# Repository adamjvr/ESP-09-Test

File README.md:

# ESP-09-Test
A simple quick breakout board to test the functionality of the ESP-09 ESP8266 module. Designed to test the modules functionality in comparison to the ESP-12E module used in the SunLEaf prototypes and the version 1 PCB that was modified.

KiCAD 3D Renders

OSHPark Board Renders

Top

Bottom

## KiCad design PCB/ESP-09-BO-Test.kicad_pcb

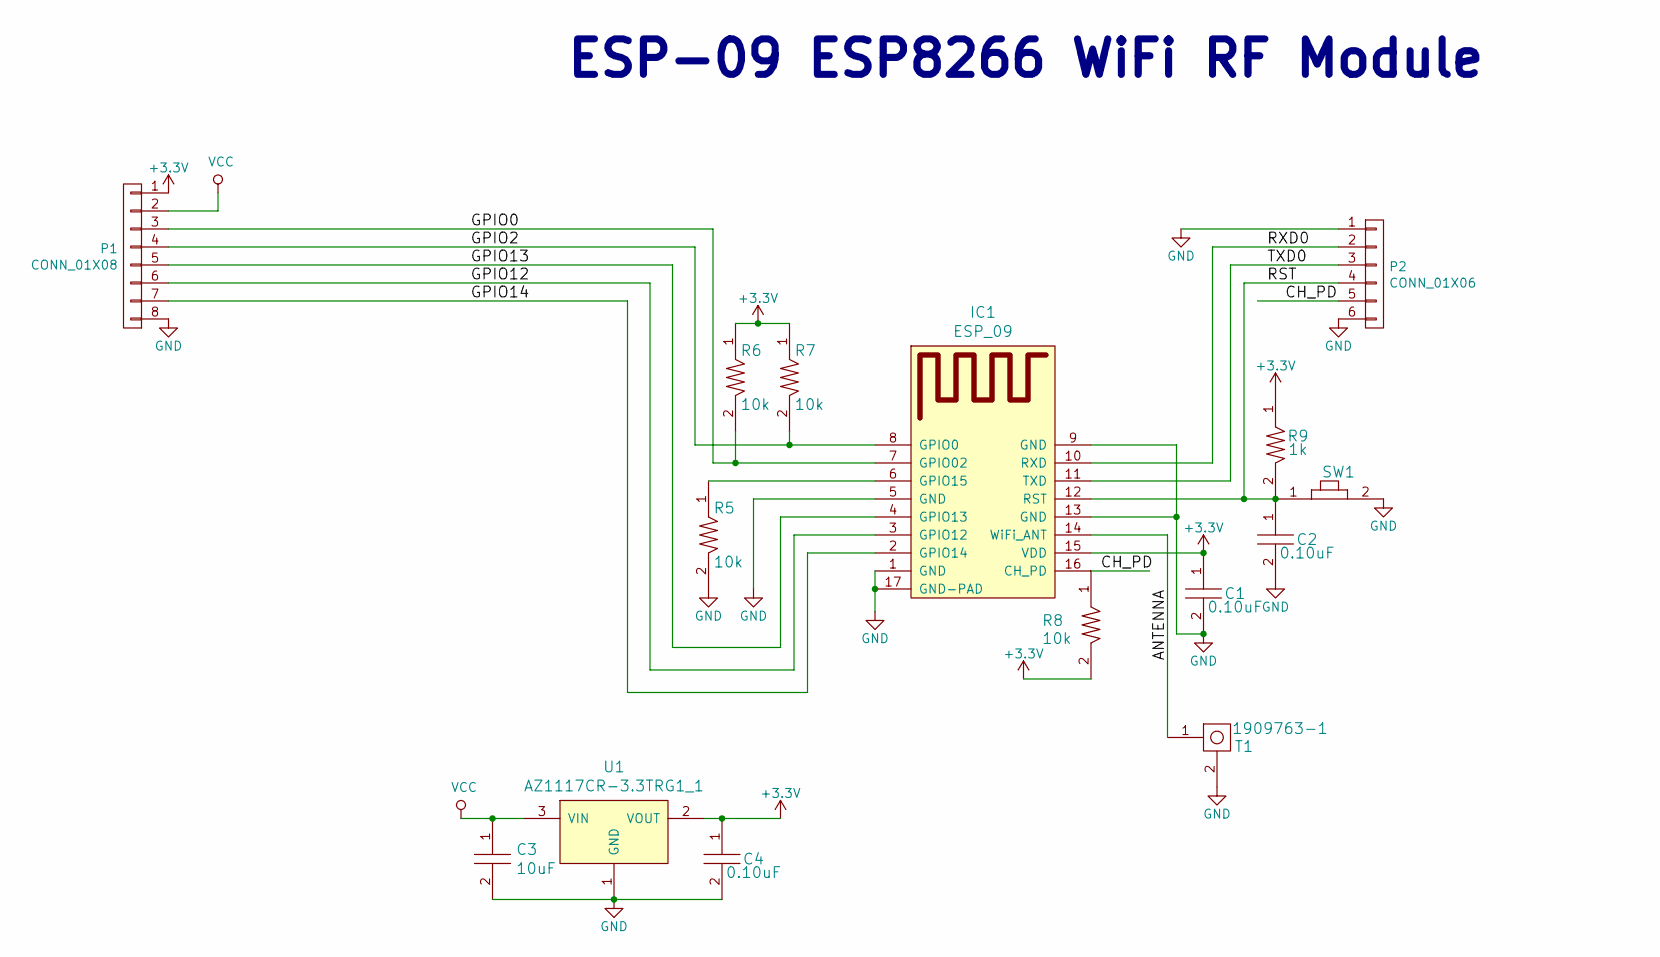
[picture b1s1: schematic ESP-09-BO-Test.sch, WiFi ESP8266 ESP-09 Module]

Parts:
C1, C2, C4: CL05B104JP5NNNC; C0402; Tolerance 5%; Voltage 10V; MFR# CL05B104JP5NNNC
C3: CL10A106KQ8NNNC; C0603; Tolerance 10%; Voltage 6.3V; MFR# CL10A106KQ8NNNC
IC1: ESP_09; ESP-09
P1: CONN_01X08; Pin_Header_Straight_1x08
P2: CONN_01X06; Pin_Header_Straight_1x06
R5, R6, R7, R8: RC1005F103CS; R0402; Tolerance 1%; Voltage N/A; MFR# RC1005F103CS
R9: RC1005F102CS; R0402; Tolerance %; Voltage N/A; MFR# RC1005F102CS
SW1: B3U-1000P; Tolerance %; Voltage 50V; MFR# B3U-1000P
T1: 1909763-1; Tolerance N/A; Voltage N/A; MFR# 1909763-1
U1: AZ1117CR-3.3TRG1_1; AZ1117CR-3.3TRG1; Tolerance N/A; Voltage 3.7V input 3.3V Output; MFR# AZ1117CR-3.3TRG1

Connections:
+3V3: C1.1, C4.1, IC1.15 (VDD), P1.1, R6.1, R7.1, R8.2, R9.1, U1.2 (VOUT)
/ANTENNA: IC1.14 (WiFi_ANT), T1.1
/CH_PD: IC1.16 (CH_PD), P2.5, R8.1
/GPIO0: IC1.7 (GPIO02), P1.3, R6.2
/GPIO2: IC1.8 (GPIO0), P1.4, R7.2
/GPIO12: IC1.3 (GPIO12), P1.6
/GPIO13: IC1.4 (GPIO13), P1.5
/GPIO14: IC1.2 (GPIO14), P1.7
/RST: C2.1, IC1.12 (RST), P2.4, R9.2, SW1.1
/RXD0: IC1.10 (RXD), P2.2
/TXD0: IC1.11 (TXD), P2.3
GND: C1.2, C2.2, C3.2, C4.2, IC1.1 (GND), IC1.5 (GND), IC1.9 (GND), IC1.13 (GND), IC1.17 (GND-PAD), P1.8, P2.1, P2.6, R5.2, SW1.2, T1.2, U1.1 (GND)
unnamed: IC1.6 (GPIO15), R5.1
VCC: C3.1, P1.2, U1.3 (VIN)

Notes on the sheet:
ESP-09 ESP8266 WiFi RF Module

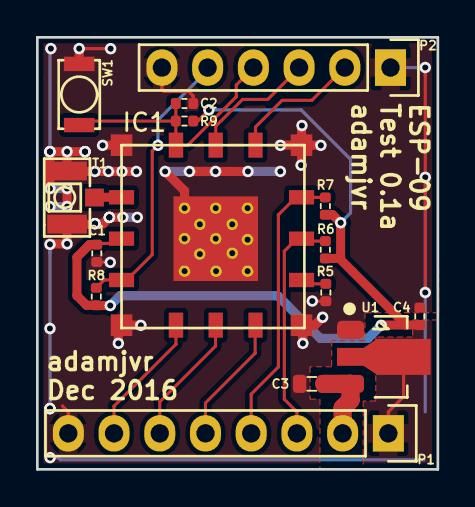
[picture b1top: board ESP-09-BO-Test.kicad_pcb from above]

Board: 2 copper layers, 22.2 x 24.0 mm, 15 parts (0 on the bottom side), 14 nets.

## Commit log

2016-12-06 Completely Done
    Schematic and PCB completely done
2016-12-06 Picture
    3D render picture added
2016-12-06 Photos and readme
    Photos added and readme edited.
2016-12-06 Markdown fix
    Markdown edited
